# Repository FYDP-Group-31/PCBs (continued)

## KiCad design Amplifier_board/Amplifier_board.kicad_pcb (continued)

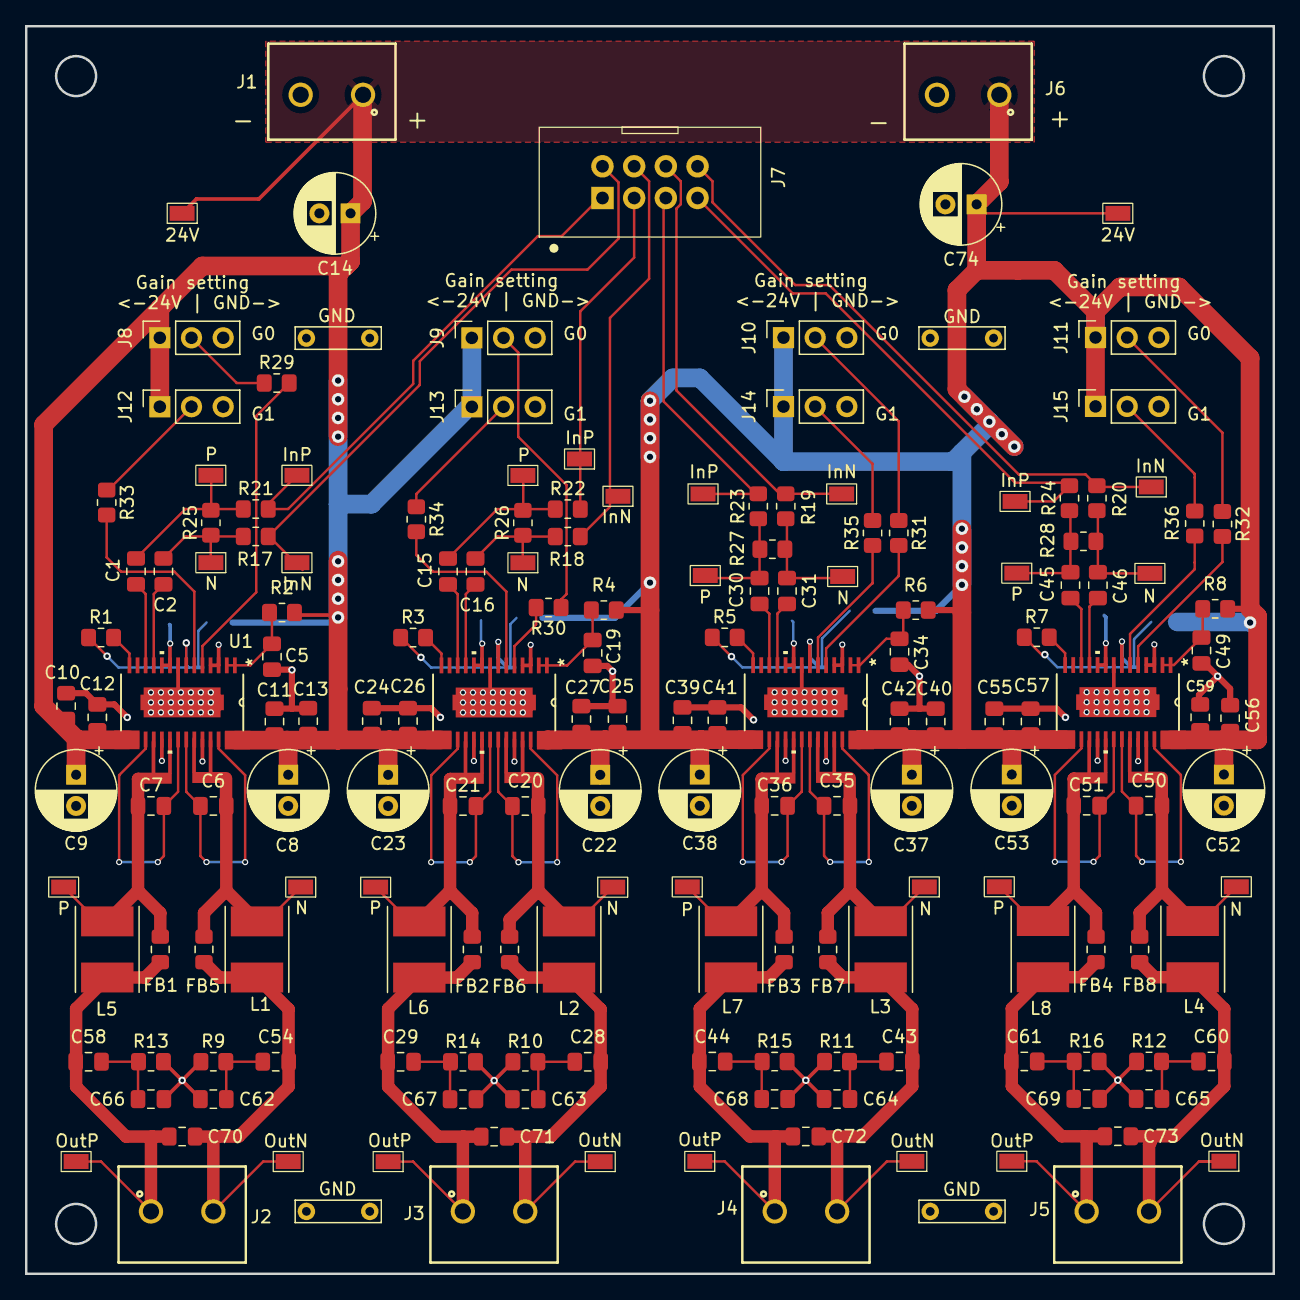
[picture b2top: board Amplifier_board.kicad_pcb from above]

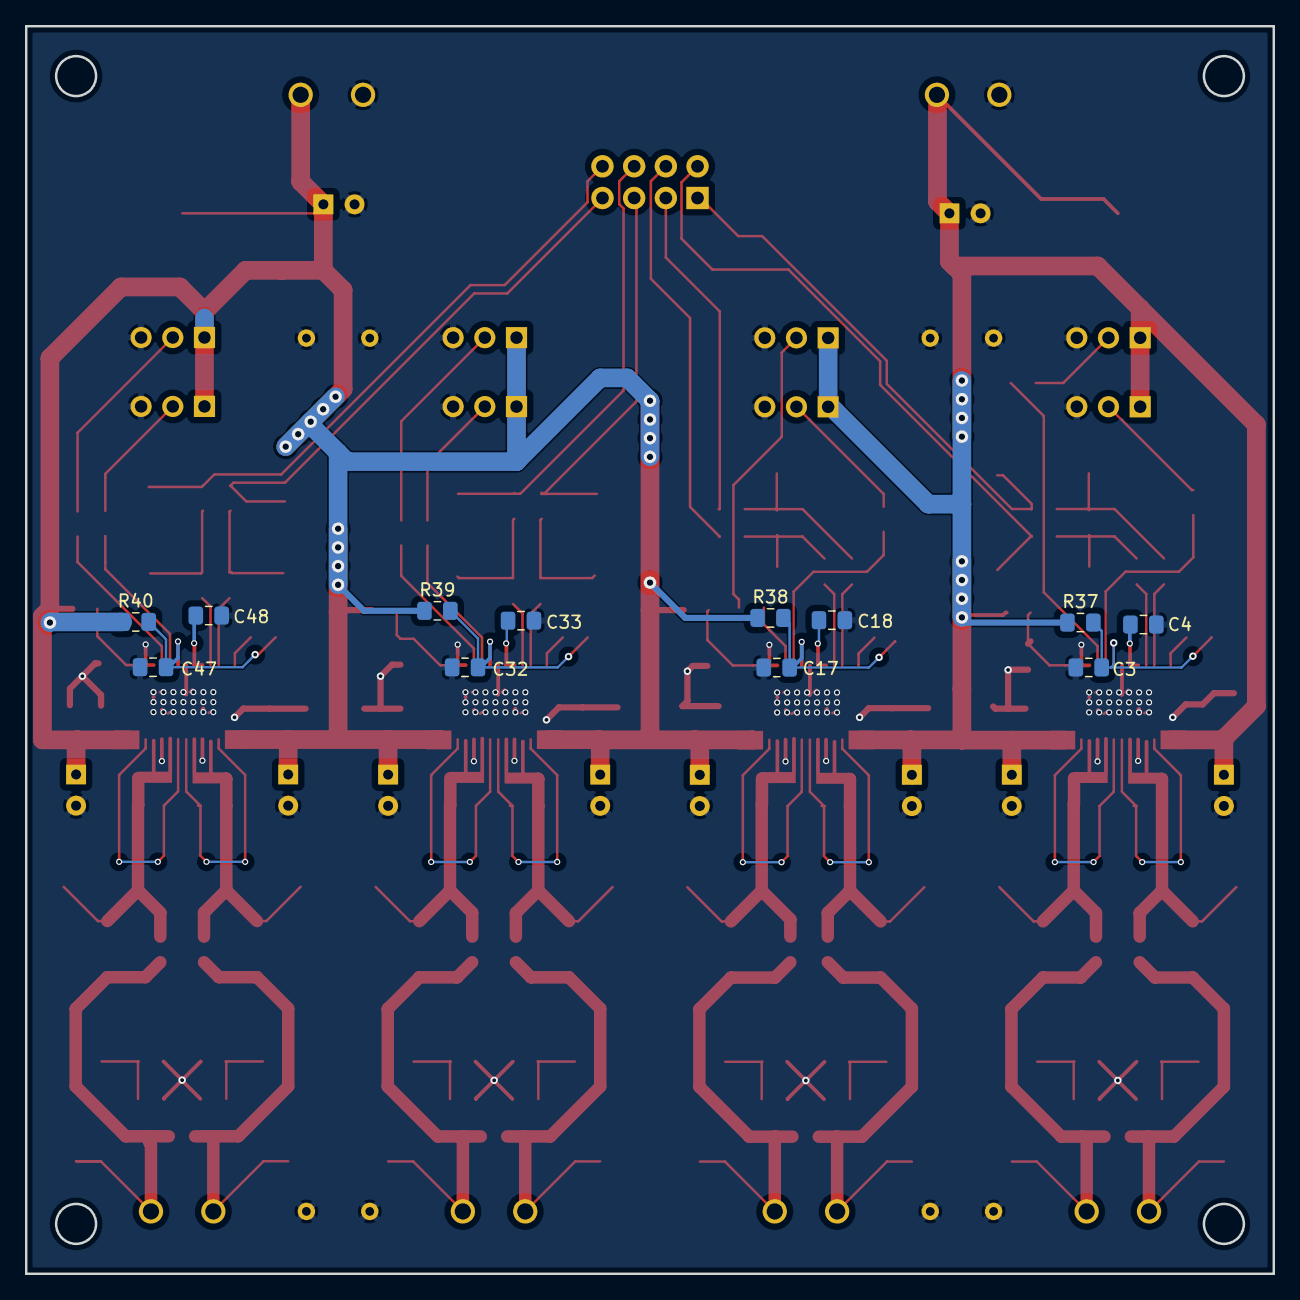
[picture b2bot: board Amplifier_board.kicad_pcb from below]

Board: 2 copper layers, 100.0 x 100.0 mm, 187 parts (12 on the bottom side), 90 nets.

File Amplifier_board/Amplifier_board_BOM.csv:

"Id";"Designator";"Footprint";"Quantity";"Designation";"Supplier and ref";
1;"U4,U3,U2,U1";"PWP28_6P17X2P4";4;"TPA3111D1PWPR";;;
2;"JP8,JP7,JP6,JP5,JP4,JP3,JP2,JP1";"R_1206_3216Metric_Pad1.30x1.75mm_HandSolder";8;"Jumper_1206";;;
3;"C74,C8,C14,C52,C53,C37,C9,C38,C23,C22";"WCAP-ASLI_6.3X7.7_DXL_";10;"100u";;;
4;"R16,R15,R14,R13,R12,R11,R10,R9";"R_0805_2012Metric_Pad1.20x1.40mm_HandSolder";8;"0";;;
5;"C73,C72,C71,C70,C69,C68,C67,C66,C65,C64,C63,C62";"C_0805_2012Metric_Pad1.18x1.45mm_HandSolder";12;"C_Small";;;
6;"J15,J14,J13,J12,J11,J10,J9,J8";"PinSocket_1x03_P2.54mm_Vertical";8;"Conn_01x03_Pin";;;
7;"C5,C56,C39,C55,C49,C40,C34,C25,C24,C19,C10,C11";"C_0805_2012Metric_Pad1.18x1.45mm_HandSolder";12;"0.1u";;;
8;"L3,L2,L4,L1,L7,L8,L6,L5";"L_Taiyo-Yuden_NR-80xx_HandSoldering";8;"68u";;;
9;"C57,C59,C41,C27,C42,C26,C12,C13";"C_0805_2012Metric_Pad1.18x1.45mm_HandSolder";8;"1000p";;;
10;"C7,C51,C35,C36,C21,C6,C50,C20";"C_0805_2012Metric_Pad1.18x1.45mm_HandSolder";8;"0.47u";;;
11;"C44,C29,C54,C58,C28,C61,C43,C60";"C_0805_2012Metric_Pad1.18x1.45mm_HandSolder";8;"0.5u";;;
12;"R7,R3,R8,R5,R6,R1,R4,R2";"R_0805_2012Metric_Pad1.20x1.40mm_HandSolder";8;"100k";;;
13;"J4,J6,J5,J1,J2,J3";"691137710002";6;"Screw Terminal";;;
14;"C48,C16,C45,C31,C4,C33,C32,C30,C47,C15,C1,C18,C2,C17,C46,C3";"C_0805_2012Metric_Pad1.18x1.45mm_HandSolder";16;"1u";;;
15;"J7";"ASSMANN_A-DF_09_A_KG-T4S";1;"A-DF_09_A_KG-T4S";;;

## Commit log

2025-06-08 Added KiCad Files
2025-06-12 Added MCU dev board, connected power pins of DAC
2025-06-23 Rough draft of amp board schematics
2025-06-23 Added buffers at DAC outputs
2025-06-26 Added 2.5V regulator circuit, jumpers on buffers
2025-06-28 Added filtering between DAC and amp, power receptacles
2025-07-02 Added footprints for amplifier board
2025-07-03 Started layout of amplifier board
2025-07-03 More progress on layout
2025-07-03 More routing on amp board
2025-07-04 Removed buffers on DAC board
2025-07-04 Added test points, almost finished layout for amp board
2025-07-05 Updated silkscreen on amp board
2025-07-07 Added new MCU board footprint and symbol
2025-07-07 Schematic almost done on DAC board
2025-07-09 Added ferrites to amp board
2025-07-10 Started layout of ADAU1966 area
2025-07-10 Separated AVDD and PVDD on amplifier board
2025-07-11 Finished layout for DAC board with 1 MCU
2025-07-11 did a thing
2025-07-11 Updated ribbon connector on amp board
2025-07-16 Changed to 4 layer board
2025-07-18 Amp board final draft
2025-07-18 Added gerbers for amp board
2025-07-20 Widened 24V trace, added triple vias for 3V3 lines, and other things
2025-07-20 made power lines heavier and added most of the test points
2026-01-15 Revised DAC board schematic
2026-01-15 Finished MCU to DAC signal routing
2026-01-16 DAC board layout (mostly) done
2026-01-20 Added DIP conector for UART connections
2026-01-21 First revision of DAC board
2026-01-23 Added via stiching, more decoupling
2026-01-26 generated gerber files
